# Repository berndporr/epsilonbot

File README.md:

# The Zeta-bot

What is the Zeta-Bot?

The Zeta-Bot is an open-source robot platform that uses the:

 - Raspberry PI 5,
 - [Parallax's Continuous Rotation Servo Motors](https://www.parallax.com/product/parallax-continuous-rotation-servo/),
 - [C1 LIDAR](https://www.slamtec.com/en/c1),
 - two [Raspberry PI V2 cameras](https://www.raspberrypi.com/products/camera-module-v2/) for stereo vision,
 - [a standard mobile phone 1700mAh power bank](https://uk.rs-online.com/web/p/power-banks/2498449).

It's based on years and years of experience making single PCB
Raspberry PI based robots. Every part has been chosen because of
extensive lab use proving its reliability over the years and because
of its solid hard- and software support.

## Hardware

The KiCad design files and BOM are in [hardware](hardware).

## Software

It's all in C++! Both cameras and LIDAR have an event driven framework with callbacks so no loops and multi-threaded by design.

 - The motor control libraries are in [wheeleddrive](wheeleddrive).
 - The cameras driver is in https://github.com/berndporr/libcamera2opencv with a demo to display one camera and in [stereo](stereo) is a QT6 based stereo viewer and disparity detector.
 - The LIDAR driver is in https://github.com/berndporr/c1lidar

## Credits

 - (c) 2026, Bernd Porr, mail@berndporr.me.uk
 - (c) 2025, Saleh AlMulla
 - (c) 2025, Yixuan Zha

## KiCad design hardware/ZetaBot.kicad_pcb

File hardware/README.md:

# Schematic files

It's been designed by KiCad 10.

The design at the moment is according to GU's workshop requirements who cannot do solderstop and need 2mm pads.

The [bom](bom.pdf) is here.

The Linear servos are simply glued with epoxy onto the PCB.

The RPI V2 cameras are soldered on the ground plane of the PCB with two stiff 2.5mm^2 wires. There seem to be no sensible camera holders about so stiff wires seem to be the best option also to adjust the cameras for stereo.

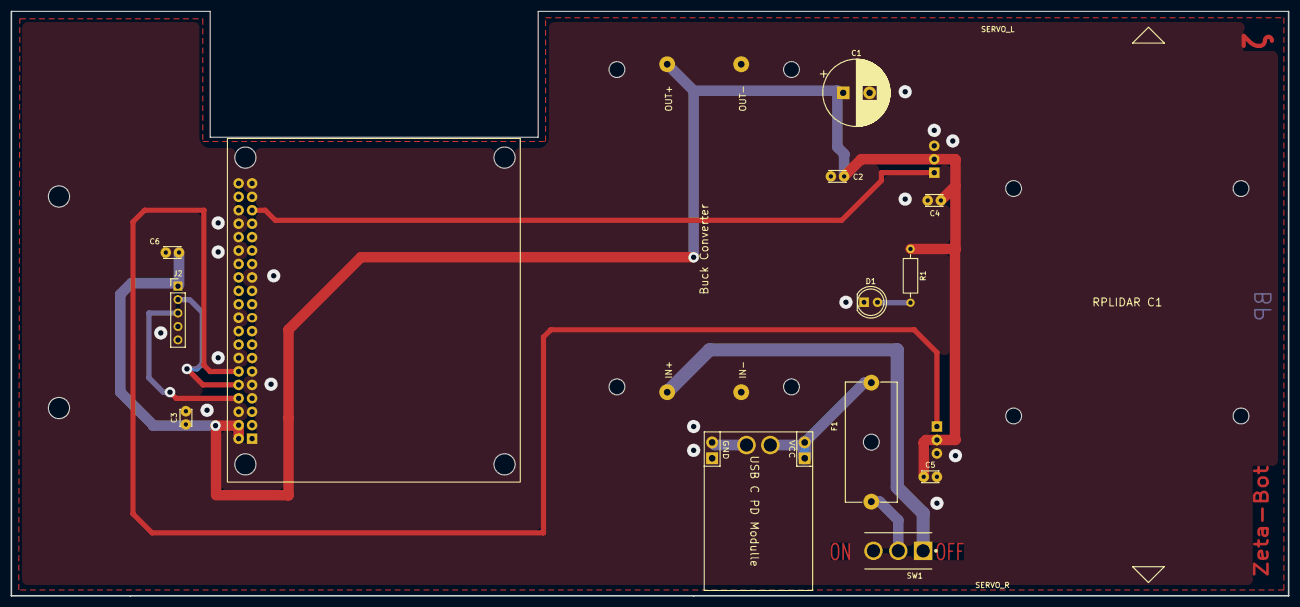
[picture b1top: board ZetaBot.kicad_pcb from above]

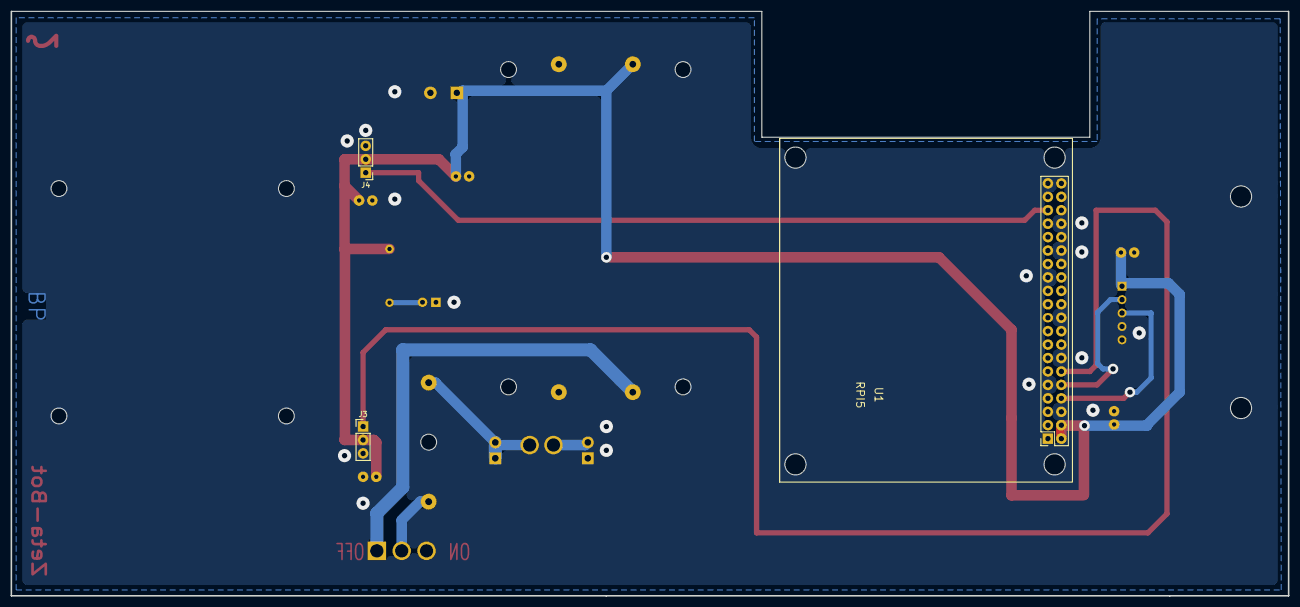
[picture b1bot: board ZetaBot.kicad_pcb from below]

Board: 2 copper layers, 241.5 x 110.5 mm, 17 parts (3 on the bottom side), 10 nets.

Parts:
C1: 2200uF; CP_Radial_D12.5mm_P5.00mm
C2, C3, C4, C5, C6: 1uF; C_Disc_D3.0mm_W2.0mm_P2.50mm
D1: LED; LED_D5.0mm_Clear
F1: Fuse; Fuseholder_Cylinder-5x20mm_Schurter_0031_8201_Horizontal_Op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
J1: USB C PD Modulle; USB_C
J2: Conn_01x05; PinHeader_1x05_P2.54mm_Vertical
J3: MOTOR_L; PinHeader_1x03_P2.54mm_Vertical
J4: MOTOR_R; PinHeader_1x03_P2.54mm_Vertical
R1: 330R; R_Axial_DIN0207_L6.3mm_D2.5mm_P10.16mm_Horizontal
SW1: SW_SPDT; TE_4-1825136-5
U1: RPLIDAR C1
U1#2: RPI5
U2: Buck Converter; BUCK_CONV

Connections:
+5V: C1.1, C2.1, C3.1, C4.1, C5.1, C6.1, J2.1, J3.2, J4.2, R1.1, U1#2.2 (5V1), U1#2.4 (5V2), U2.3 (OUT+)
+9V: SW1.1 (A), U2.1 (IN+)
GND: C1.2, C2.2, C3.2, C4.2, C5.2, C6.2, D1.1 (K), J1.2 (GND), J1.4 (GND), J2.4, J3.3, J4.3, U1#2.6 (GND1), U1#2.9 (GND8), U1#2.14 (GND2), U1#2.20 (GND3), U1#2.25 (GND7), U1#2.30 (GND4), U1#2.34 (GND5), U1#2.39 (GND6), U2.2 (IN-), U2.4 (OUT-)
LIDAR_RX: J2.3, U1#2.8 (GPIO14_UART/TX)
LIDAR_TX: J2.2, U1#2.10 (GPIO15_UART/RX)
unnamed: D1.2 (A), R1.2
unnamed: F1.2, J1.1 (VCC), J1.3 (VCC)
unnamed: F1.1, SW1.2 (B)
PWM_L: J4.1, U1#2.35 (GPIO19_PWM0/CHAN2)
PWM_R: J3.1, U1#2.12 (GPIO18_PWM0/CHAN2)

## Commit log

2026-04-09 Initial commit which is still the deltabot!
2026-04-09 Updated PCB layout for the RPI
2026-04-12 Added missing files
2026-04-12 Added a new footprint for the USB C PD.
2026-04-14 Added PDF
2026-04-15 Added readme
2026-04-15 Removed references to alphabot
2026-04-15 Added photo
2026-04-26 Added info about the schematic.
2026-04-26 Added screenshot
2026-04-26 Added instructions
2026-04-26 Changed it to "hardware".
2026-04-26 Link to stereo
2026-04-26 Rotated it.
2026-05-12 removed global variable!
2026-05-12 added a half-baked program to test wheel speed. Need to get rubber coats for wheels
2026-05-19 changed program test speed

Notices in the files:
hardware/ZetaBot.kicad_pcb:
GPL
